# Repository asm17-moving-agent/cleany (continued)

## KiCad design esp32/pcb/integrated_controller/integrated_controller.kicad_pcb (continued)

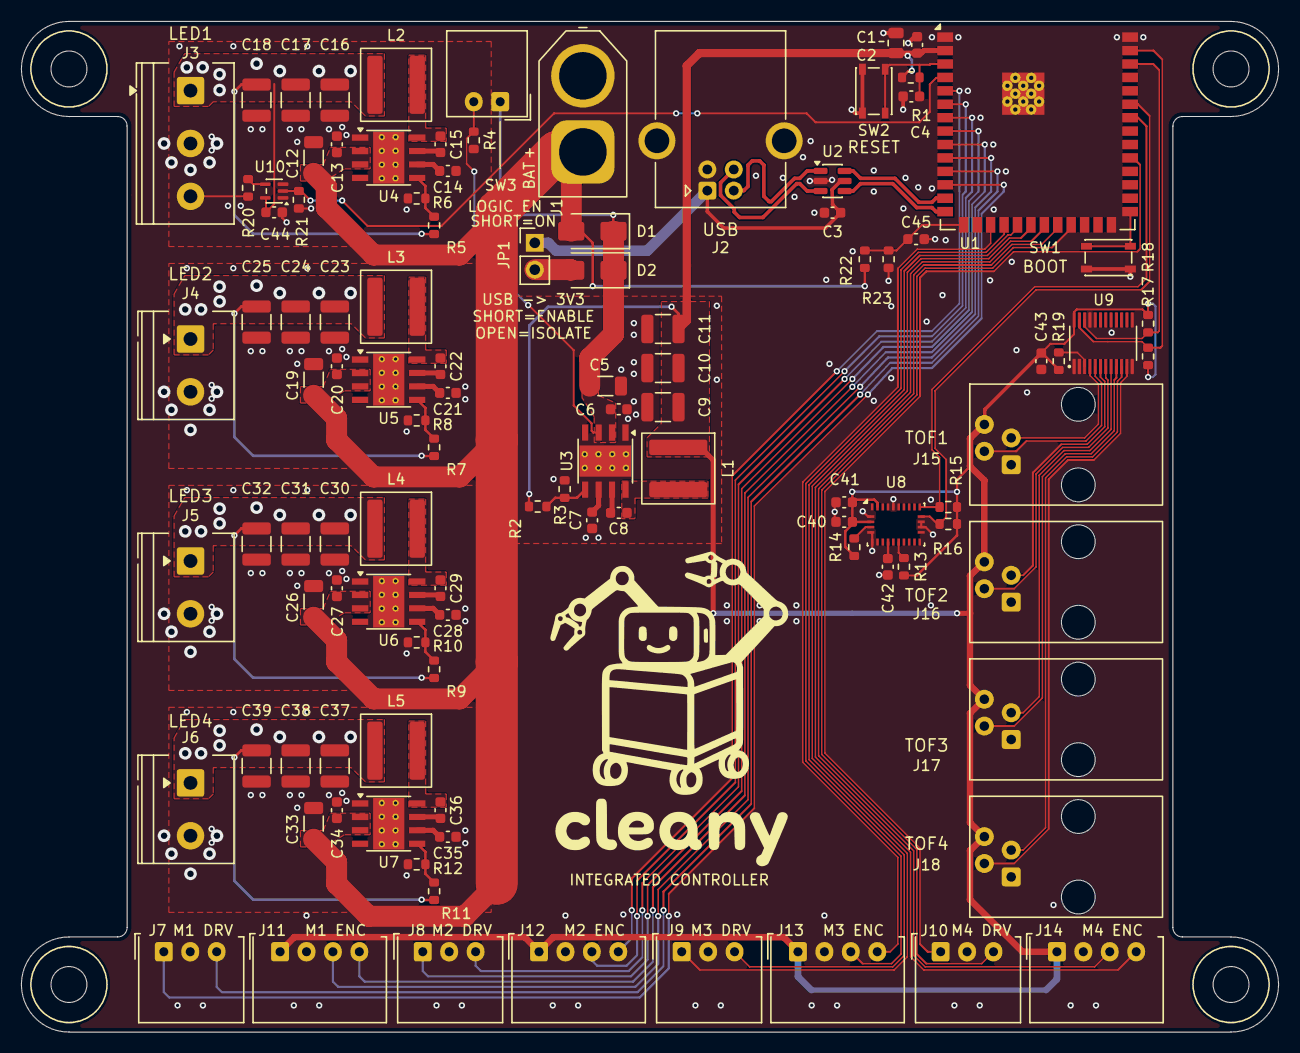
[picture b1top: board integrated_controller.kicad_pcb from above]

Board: 2 copper layers, 119.0 x 95.6 mm, 111 parts (0 on the bottom side), 73 nets.

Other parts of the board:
H1, H2, H3, H4: M3 clearance; MountingHole_3.4mm_M3_Head7mm

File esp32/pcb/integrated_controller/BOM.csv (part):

Reference,Quantity,Value,Manufacturer,MPN,Specification,Footprint,FootprintStatus,Datasheet,Supplier,SupplierSKU,PurchaseURL,DisplayedStock,StockChecked,MOQ,OrderMultiple,SupplyStatus
C1,1,10u,TDK,C2012X5R1E106K125DB,"10 µF ±10%, 25 V, X5R, 0805",Capacitor_SMD:C_0805_2012Metric,Assigned,,DigiKey,445-C2012X5R1E106K125DBCT-ND,https://www.digikey.kr/en/products/detail/tdk/C2012X5R1E106K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,20,2026-10-29 KST,1,1,표시 재고
C2,1,100n,KEMET,C0603C104K5RACTU,"100 nF ±10%, 50 V, X7R, 0603",Capacitor_SMD:C_0603_1608Metric,Assigned,https://yageogroup.com/content/datasheet/asset/file/KEM_C100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,DigiKey,,https://www.digikey.kr/en/products/detail/kemet/C0603C104K5R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,3451761,2026-10-29 KST,결제 시 확인,결제 시 확인,표시 재고
C3,1,100n,KEMET,C0603C104K5RACTU,"100 nF ±10%, 50 V, X7R, 0603",Capacitor_SMD:C_0603_1608Metric,Assigned,https://yageogroup.com/content/datasheet/asset/file/KEM_C100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,DigiKey,,https://www.digikey.kr/en/products/detail/kemet/C0603C104K5R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,3451761,2026-10-29 KST,결제 시 확인,결제 시 확인,표시 재고
C4,1,1u,KEMET,C0603C105K4RACTU,"1 µF ±10%, 16 V, X7R, 0603",Capacitor_SMD:C_0603_1608Metric,Assigned,https://yageogroup.com/content/datasheet/asset/file/KEM_C100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,DigiKey,,https://www.digikey.kr/en/products/detail/kemet/C0603C105K4R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,3208535,2026-10-29 KST,결제 시 확인,결제 시 확인,표시 재고
C5,1,10u,"Cal-Chip Electronics, Inc.",GMC31X5R106K50NT,"10 µF ±10%, 50 V, X5R, 1206; 3.2 × 1.6 mm, height ≤1.90 mm",Capacitor_SMD:C_1206_3216Metric,Assigned,https://calchip.com/wp-content/uploads/2025/05/GMC-Series-3.pdf,DigiKey,4713-GMC31X5R106K50NTCT-ND,https://www.digikey.kr/en/products/detail/cal-chip-electroni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,93418,2026-10-29 KST,1,1,표시 재고; CT
C6,1,220n,Murata Electronics,GRM188R71H224KAC4D,"220 nF ±10%, 50 V, X7R, 0603",Capacitor_SMD:C_0603_1608Metric,Assigned,,DigiKey,,https://www.digikey.kr/en/products/detail/murata-electronics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,136343,2026-10-29 KST,결제 시 확인,결제 시 확인,표시 재고
C7,1,1u,Samsung Electro-Mechanics,CL10B105MO8NNWC,"1 µF ±20%, 16 V, X7R, 0603",Capacitor_SMD:C_0603_1608Metric,Assigned,https://mm.digikey.com/Volume0/opasdata/d220001/medias/docus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,DigiKey,,https://www.digikey.kr/en/products/detail/samsung-electro-me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,386926,2026-10-29 KST,결제 시 확인,결제 시 확인,표시 재고
C8,1,100n,KYOCERA AVX,KGM15BR71E104KT,"100 nF ±10%, 25 V, X7R, 0603",Capacitor_SMD:C_0603_1608Metric,Assigned,https://search.kyocera-avx.com/product/KGM15BR71E104KT,DigiKey,478-KGM15BR71E104KTCT-ND,https://www.digikey.kr/en/products/detail/kyocera-avx/KGM15B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,690105,2026-10-29 KST,결제 시 확인,결제 시 확인,표시 재고
C9,1,22u,TDK,CGA6P1X7R1C226M250AC,"22 µF ±20%, 16 V, X7R, 1210, AEC-Q200",Capacitor_SMD:C_1210_3225Metric,Assigned,https://product.tdk.com/system/files/dam/doc/product/capacit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,DigiKey,,https://www.digikey.kr/en/products/detail/tdk-corporation/CG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,31065,2026-10-29 KST,결제 시 확인,결제 시 확인,표시 재고
C10,1,22u,TDK,CGA6P1X7R1C226M250AC,"22 µF ±20%, 16 V, X7R, 1210, AEC-Q200",Capacitor_SMD:C_1210_3225Metric,Assigned,https://product.tdk.com/system/files/dam/doc/product/capacit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,DigiKey,,https://www.digikey.kr/en/products/detail/tdk-corporation/CG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,31065,2026-10-29 KST,결제 시 확인,결제 시 확인,표시 재고
C11,1,22u,TDK,CGA6P1X7R1C226M250AC,"22 µF ±20%, 16 V, X7R, 1210, AEC-Q200",Capacitor_SMD:C_1210_3225Metric,Assigned,https://product.tdk.com/system/files/dam/doc/product/capacit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,DigiKey,,https://www.digikey.kr/en/products/detail/tdk-corporation/CG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,31065,2026-10-29 KST,결제 시 확인,결제 시 확인,표시 재고
C12,1,10u,"Cal-Chip Electronics, Inc.",GMC31X5R106K50NT,"10 µF ±10%, 50 V, X5R, 1206; 3.2 × 1.6 mm, height ≤1.90 mm",Capacitor_SMD:C_1206_3216Metric,Assigned,https://calchip.com/wp-content/uploads/2025/05/GMC-Series-3.pdf,DigiKey,4713-GMC31X5R106K50NTCT-ND,https://www.digikey.kr/en/products/detail/cal-chip-electroni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,93418,2026-10-29 KST,1,1,표시 재고; CT
C13,1,220n,Murata Electronics,GRM188R71H224KAC4D,"220 nF ±10%, 50 V, X7R, 0603",Capacitor_SMD:C_0603_1608Metric,Assigned,,DigiKey,,https://www.digikey.kr/en/products/detail/murata-electronics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,136343,2026-10-29 KST,결제 시 확인,결제 시 확인,표시 재고
C14,1,1u,Samsung Electro-Mechanics,CL10B105MO8NNWC,"1 µF ±20%, 16 V, X7R, 0603",Capacitor_SMD:C_0603_1608Metric,Assigned,https://mm.digikey.com/Volume0/opasdata/d220001/medias/docus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,DigiKey,,https://www.digikey.kr/en/products/detail/samsung-electro-me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,386926,2026-10-29 KST,결제 시 확인,결제 시 확인,표시 재고
C15,1,100n,KYOCERA AVX,KGM15BR71E104KT,"100 nF ±10%, 25 V, X7R, 0603",Capacitor_SMD:C_0603_1608Metric,Assigned,https://search.kyocera-avx.com/product/KGM15BR71E104KT,DigiKey,478-KGM15BR71E104KTCT-ND,https://www.digikey.kr/en/products/detail/kyocera-avx/KGM15B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,690105,2026-10-29 KST,결제 시 확인,결제 시 확인,표시 재고
C16,1,22u,TDK,CGA6P1X7R1C226M250AC,"22 µF ±20%, 16 V, X7R, 1210, AEC-Q200",Capacitor_SMD:C_1210_3225Metric,Assigned,https://product.tdk.com/system/files/dam/doc/product/capacit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,DigiKey,,https://www.digikey.kr/en/products/detail/tdk-corporation/CG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,31065,2026-10-29 KST,결제 시 확인,결제 시 확인,표시 재고
C17,1,22u,TDK,CGA6P1X7R1C226M250AC,"22 µF ±20%, 16 V, X7R, 1210, AEC-Q200",Capacitor_SMD:C_1210_3225Metric,Assigned,https://product.tdk.com/system/files/dam/doc/product/capacit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,DigiKey,,https://www.digikey.kr/en/products/detail/tdk-corporation/CG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,31065,2026-10-29 KST,결제 시 확인,결제 시 확인,표시 재고
C18,1,22u,TDK,CGA6P1X7R1C226M250AC,"22 µF ±20%, 16 V, X7R, 1210, AEC-Q200",Capacitor_SMD:C_1210_3225Metric,Assigned,https://product.tdk.com/system/files/dam/doc/product/capacit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,DigiKey,,https://www.digikey.kr/en/products/detail/tdk-corporation/CG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,31065,2026-10-29 KST,결제 시 확인,결제 시 확인,표시 재고
C19,1,10u,"Cal-Chip Electronics, Inc.",GMC31X5R106K50NT,"10 µF ±10%, 50 V, X5R, 1206; 3.2 × 1.6 mm, height ≤1.90 mm",Capacitor_SMD:C_1206_3216Metric,Assigned,https://calchip.com/wp-content/uploads/2025/05/GMC-Series-3.pdf,DigiKey,4713-GMC31X5R106K50NTCT-ND,https://www.digikey.kr/en/products/detail/cal-chip-electroni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,93418,2026-10-29 KST,1,1,표시 재고; CT
C20,1,220n,Murata Electronics,GRM188R71H224KAC4D,"220 nF ±10%, 50 V, X7R, 0603",Capacitor_SMD:C_0603_1608Metric,Assigned,,DigiKey,,https://www.digikey.kr/en/products/detail/murata-electronics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,136343,2026-10-29 KST,결제 시 확인,결제 시 확인,표시 재고
C21,1,1u,Samsung Electro-Mechanics,CL10B105MO8NNWC,"1 µF ±20%, 16 V, X7R, 0603",Capacitor_SMD:C_0603_1608Metric,Assigned,https://mm.digikey.com/Volume0/opasdata/d220001/medias/docus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,DigiKey,,https://www.digikey.kr/en/products/detail/samsung-electro-me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,386926,2026-10-29 KST,결제 시 확인,결제 시 확인,표시 재고
C22,1,100n,KYOCERA AVX,KGM15BR71E104KT,"100 nF ±10%, 25 V, X7R, 0603",Capacitor_SMD:C_0603_1608Metric,Assigned,https://search.kyocera-avx.com/product/KGM15BR71E104KT,DigiKey,478-KGM15BR71E104KTCT-ND,https://www.digikey.kr/en/products/detail/kyocera-avx/KGM15B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,690105,2026-10-29 KST,결제 시 확인,결제 시 확인,표시 재고
C23,1,22u,TDK,CGA6P1X7R1C226M250AC,"22 µF ±20%, 16 V, X7R, 1210, AEC-Q200",Capacitor_SMD:C_1210_3225Metric,Assigned,https://product.tdk.com/system/files/dam/doc/product/capacit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,DigiKey,,https://www.digikey.kr/en/products/detail/tdk-corporation/CG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,31065,2026-10-29 KST,결제 시 확인,결제 시 확인,표시 재고
C24,1,22u,TDK,CGA6P1X7R1C226M250AC,"22 µF ±20%, 16 V, X7R, 1210, AEC-Q200",Capacitor_SMD:C_1210_3225Metric,Assigned,https://product.tdk.com/system/files/dam/doc/product/capacit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,DigiKey,,https://www.digikey.kr/en/products/detail/tdk-corporation/CG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,31065,2026-10-29 KST,결제 시 확인,결제 시 확인,표시 재고
C25,1,22u,TDK,CGA6P1X7R1C226M250AC,"22 µF ±20%, 16 V, X7R, 1210, AEC-Q200",Capacitor_SMD:C_1210_3225Metric,Assigned,https://product.tdk.com/system/files/dam/doc/product/capacit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,DigiKey,,https://www.digikey.kr/en/products/detail/tdk-corporation/CG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,31065,2026-10-29 KST,결제 시 확인,결제 시 확인,표시 재고
C26,1,10u,"Cal-Chip Electronics, Inc.",GMC31X5R106K50NT,"10 µF ±10%, 50 V, X5R, 1206; 3.2 × 1.6 mm, height ≤1.90 mm",Capacitor_SMD:C_1206_3216Metric,Assigned,https://calchip.com/wp-content/uploads/2025/05/GMC-Series-3.pdf,DigiKey,4713-GMC31X5R106K50NTCT-ND,https://www.digikey.kr/en/products/detail/cal-chip-electroni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,93418,2026-10-29 KST,1,1,표시 재고; CT
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
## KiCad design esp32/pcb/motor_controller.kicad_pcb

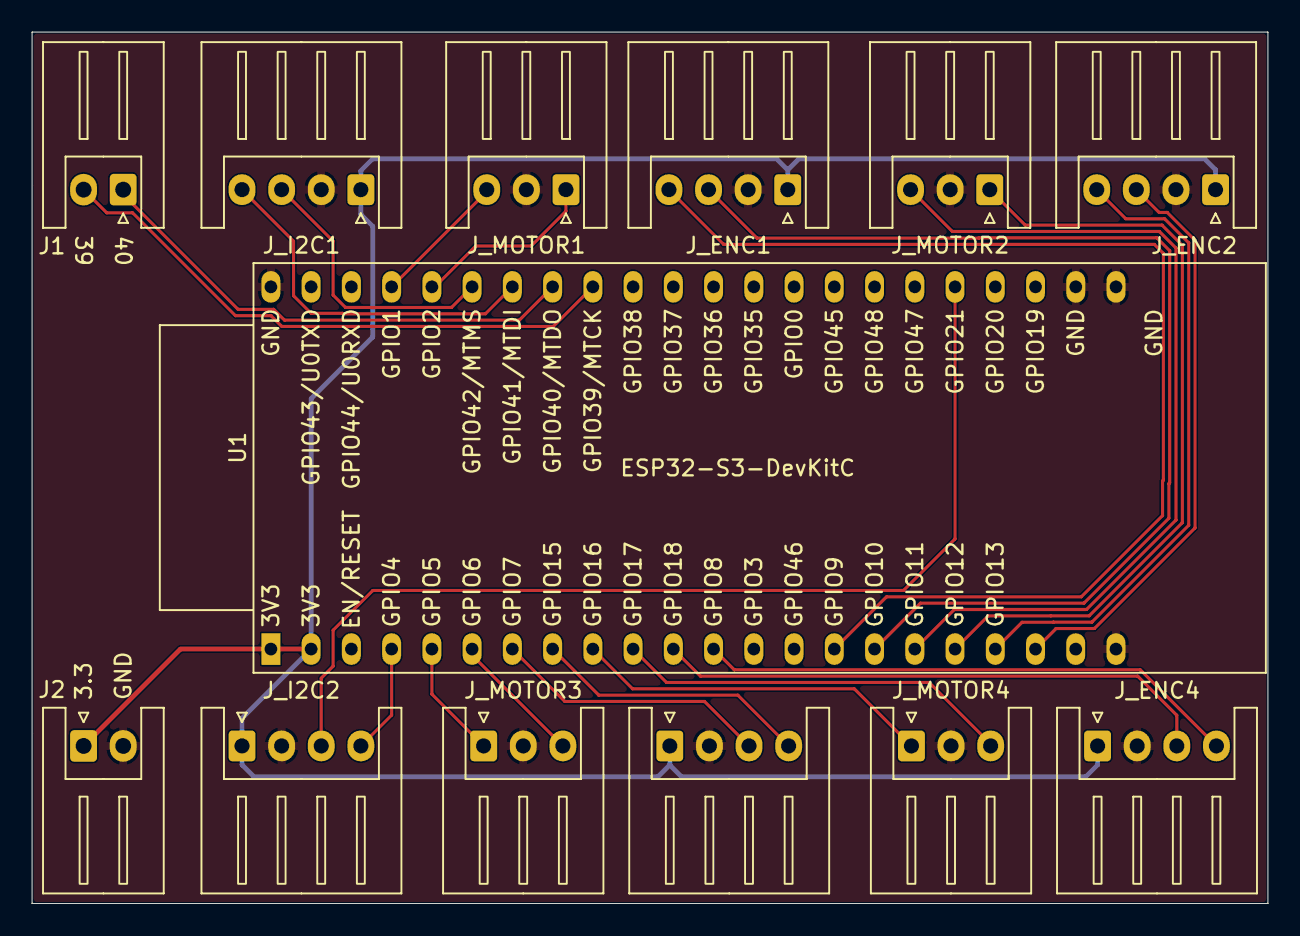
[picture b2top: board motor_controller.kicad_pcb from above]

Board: 2 copper layers, 78.0 x 55.0 mm, 13 parts (0 on the bottom side), 24 nets.

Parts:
J1, J2: JST_XH; JST_XH_S2B-XH-A_1x02_P2.50mm_Horizontal
J_ENC1, J_ENC2, J_ENC3, J_ENC4: JST_XH; JST_XH_S4B-XH-A_1x04_P2.50mm_Horizontal
J_I2C1, J_I2C2: JST_XH; JST_XH_S4B-XH-A_1x04_P2.50mm_Horizontal
J_MOTOR1, J_MOTOR2, J_MOTOR3, J_MOTOR4: JST_XH; JST_XH_S3B-XH-A_1x03_P2.50mm_Horizontal
U1: ESP32-S3-DevKitC

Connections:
+3V3: J2.1, J_ENC1.1, J_ENC2.1, J_ENC3.1, J_ENC4.1, J_I2C1.1, J_I2C2.1, U1.1 (3V3), U1.2 (3V3)
/ENC1_A_RAW: J_ENC1.3, U1.16 (GPIO10/ADC1_CH9)
/ENC1_B_RAW: J_ENC1.4, U1.15 (GPIO9/ADC1_CH8)
/ENC2_A_RAW: J_ENC2.3, U1.20 (GPIO14/ADC2_CH3)
/ENC2_B_RAW: J_ENC2.4, U1.19 (GPIO13/ADC2_CH2)
/ENC3_A_RAW: J_ENC3.3, U1.7 (GPIO7/ADC1_CH6)
/ENC3_B_RAW: J_ENC3.4, U1.8 (GPIO15/ADC2_CH4/32K_P)
/ENC4_A_RAW: J_ENC4.3, U1.11 (GPIO18/ADC2_CH7)
/ENC4_B_RAW: J_ENC4.4, U1.12 (GPIO8/ADC1_CH7)
/I2C1_SCL: J_I2C1.3, U1.39 (GPIO42/MTMS)
/I2C1_SDA: J_I2C1.4, U1.38 (GPIO41/MTDI)
/I2C2_SCL: J_I2C2.3, U1.27 (GPIO21)
/I2C2_SDA: J_I2C2.4, U1.4 (GPIO4/ADC1_CH3)
/M1_DIR: J_MOTOR1.3, U1.41 (GPIO1/ADC1_CH0)
/M1_PWM: J_MOTOR1.1, U1.40 (GPIO2/ADC1_CH1)
/M2_DIR: J_MOTOR2.3, U1.17 (GPIO11/ADC2_CH0)
/M2_PWM: J_MOTOR2.1, U1.18 (GPIO12/ADC2_CH1)
/M3_DIR: J_MOTOR3.3, U1.6 (GPIO6/ADC1_CH5)
/M3_PWM: J_MOTOR3.1, U1.5 (GPIO5/ADC1_CH4)
/M4_DIR: J_MOTOR4.3, U1.10 (GPIO17/ADC2_CH6)
/M4_PWM: J_MOTOR4.1, U1.9 (GPIO16/ADC2_CH5/32K_N)
GND: J2.2, J_ENC1.2, J_ENC2.2, J_ENC3.2, J_ENC4.2, J_I2C1.2, J_I2C2.2, J_MOTOR1.2, J_MOTOR2.2, J_MOTOR3.2, J_MOTOR4.2, U1.22 (GND), U1.23 (GND), U1.24 (GND), U1.44 (GND)
unnamed: J1.1, U1.37 (GPIO40/MTDO)
unnamed: J1.2, U1.36 (GPIO39/MTCK)
